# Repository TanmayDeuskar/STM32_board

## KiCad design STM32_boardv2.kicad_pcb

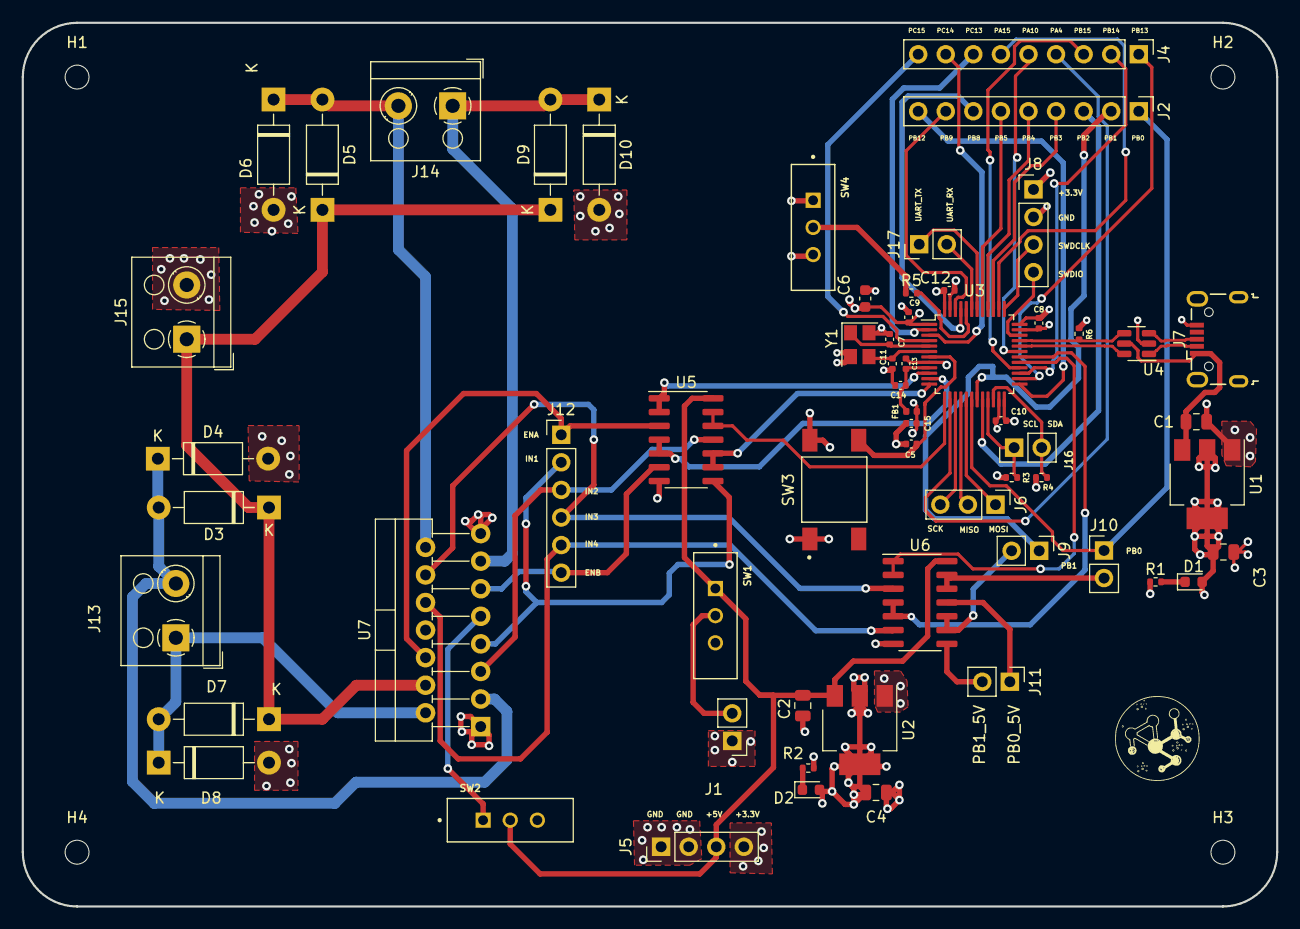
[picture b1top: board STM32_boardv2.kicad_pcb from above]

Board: 4 copper layers, 115.5 x 81.4 mm, 64 parts (0 on the bottom side), 66 nets.

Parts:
C1, C2, C3, C4: 22u; C_0805_2012Metric
C5, C8, C9, C10, C12: 100n; C_0402_1005Metric
C6: 10u; C_0603_1608Metric
C7, C11: 27p; C_0402_1005Metric
C13: 10n; C_0402_1005Metric
C14, C15: 1u; C_0402_1005Metric
D1, D2: LED; LED_0603_1608Metric
D3, D4, D5, D6, D7, D8, D9, D10: 1N4007; D_DO-41_SOD81_P10.16mm_Horizontal
FB1: 120R; L_0402_1005Metric
H1, H2, H3, H4: MountingHole; MountingHole_2.2mm_M2
J1, J9, J10, J11, J16, J17: Conn_01x02_Pin; PinHeader_1x02_P2.54mm_Vertical
J2, J4: Conn_01x09_Pin; PinHeader_1x09_P2.54mm_Vertical
J5, J8: Conn_01x04_Pin; PinHeader_1x04_P2.54mm_Vertical
J6: Conn_01x03_Pin; PinHeader_1x03_P2.54mm_Vertical
J7: USB_B_Micro; USB_Micro-B_Wuerth_629105150521
J12: Conn_01x06_Pin; PinHeader_1x06_P2.54mm_Vertical
J13, J14, J15: Screw_Terminal_01x02; TerminalBlock_RND_205-00001_1x02_P5.00mm_Horizontal
R1, R2, R3, R4, R6: 1K5; R_0402_1005Metric
R5: 10K; R_0402_1005Metric
SW1, SW2, SW4: SW_SPDT; SW_MINI-SPDT-SW
SW3: SW_MEC_5G; SW_4-1437565-1
U1, U2: AMS1117-3.3; SOT-223-3_TabPin2
U3: STM32F103C8T6; LQFP-48_7x7mm_P0.5mm
U4: USBLC6-2SC6; SOT-23-6
U5, U6: SN74HCT08N; SO-14_3.9x8.65mm_P1.27mm
U7: L298N; TO-220-15_P2.54x2.54mm_StaggerOdd_Lead4.58mm_Vertical
Y1: 16MHz; Crystal_SMD_3225-4Pin_3.2x2.5mm

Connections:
+3.3V: C3.1, C4.1, C6.1, C8.1, C9.1, C10.1, C12.1, C15.1, D1.2 (A), D2.2 (A), FB1.2, J5.4, J8.1, R3.1, R4.1, R6.1, SW4.3 (C), U1.2 (VO), U2.2 (VO), U3.1 (VBAT), U3.24 (VDD), U3.36 (VDD), U3.48 (VDD)
+3.3VA: C13.1, C14.1, FB1.1, U3.9 (VDDA)
+5V: C2.1, J5.3, SW1.1 (A), SW2.2 (B), U2.3 (VI), U5.14 (VCC), U6.14 (VCC)
+12V: D3.1 (K), D5.1 (K), D7.1 (K), D9.1 (K), J15.1, U7.4 (Vs)
/BOOT0: R5.2, U3.44 (BOOT0)
/CR_IN: C7.1, U3.5 (PD0), Y1.1
/CR_OUT: C11.1, U3.6 (PD1), Y1.3
/I2C2_SCL: J16.1, R3.2, U3.21 (PB10)
/I2C2_SDA: J16.2, R4.2, U3.22 (PB11)
/NRST: C5.1, SW3.3 (B), SW3.4 (B), U3.7 (NRST)
/SPI1_MISO: J6.2, U3.16 (PA6)
/SPI1_MOSI: J6.1, U3.17 (PA7)
/SPI1_SCK: J6.3, U3.15 (PA5)
/SWDCLK: J8.3, U3.37 (PA14)
/SWDIO: J8.4, U3.34 (PA13)
/SW_BOOT0: R5.1, SW4.2 (B)
/USART1_RX: J17.2, U3.43 (PB7)
/USART1_TX: J17.1, U3.42 (PB6)
/USB_CONN_D+: J7.3 (D+), U4.3 (I/O2)
/USB_CONN_D-: J7.2 (D-), U4.1 (I/O1)
/VIN: J1.2, SW1.2 (B)
ENA: J12.1, U5.3 (1Y), U7.6 (EnA)
ENB: J12.6, U5.6 (2Y), U7.11 (EnB)
GND: C1.2, C2.2, C3.2, C4.2, C5.2, C6.2, C7.2, C8.2, C9.2, C10.2, C11.2, C12.2, C13.2, C14.2, C15.2, D4.2 (A), D6.2 (A), D8.2 (A), D10.2 (A), J1.1, J5.1, J5.2, J7.5 (GND), J8.2, J15.2, R1.1, R2.1, SW3.1 (A), SW3.2 (A), SW4.1 (A), U1.1 (GND), U2.1 (GND), U3.8 (VSSA), U3.23 (VSS), U3.35 (VSS), U3.47 (VSS), U4.2 (GND), U5.7 (GND), U6.7 (GND), U7.1 (SENSE_A), U7.8 (GND), U7.15 (SENSE_B), Y1.2, Y1.4
IN1: J12.2, U5.8 (3Y), U7.7 (IN2)
IN2: J12.3, U5.11 (4Y), U7.5 (IN1)
IN3: J12.4, U6.3 (1Y), U7.12 (IN4)
IN4: J12.5, U6.6 (2Y), U7.10 (IN3)
unnamed: D1.1 (K), R1.2
unnamed: D2.1 (K), R2.2
unnamed: J9.2, U6.9 (3A), U6.10 (3B)
unnamed: J10.2, U6.12 (4A), U6.13 (4B)
unnamed: J11.1, U6.11 (4Y)
unnamed: J11.2, U6.8 (3Y)
unnamed: SW2.1 (A), U7.9 (Vss)
unnamed: U3.10 (PA0), U5.1 (1A), U5.2 (1B)
unnamed: U3.11 (PA1), U5.4 (2A), U5.5 (2B)
unnamed: U3.12 (PA2), U5.9 (3A), U5.10 (3B)
unnamed: U3.13 (PA3), U5.12 (4A), U5.13 (4B)
OUT1: D7.2 (A), D8.1 (K), J13.1, U7.2 (OUT1)
OUT2: D3.2 (A), D4.1 (K), J13.2, U7.3 (OUT2)
OUT3: D9.2 (A), D10.1 (K), J14.1, U7.13 (OUT3)
OUT4: D5.2 (A), D6.1 (K), J14.2, U7.14 (OUT4)
PA4: J4.4, U3.14 (PA4)
PA10: J4.5, U3.31 (PA10)
PA15: J4.6, U3.38 (PA15)
PB0: J2.1, J10.1, U3.18 (PB0)
PB1: J2.2, J9.1, U3.19 (PB1)
PB2: J2.3, U3.20 (PB2)
PB3: J2.4, U3.39 (PB3)
PB4: J2.5, U3.40 (PB4)
PB5: J2.6, U3.41 (PB5)
PB8: J2.7, U3.45 (PB8)
PB9: J2.8, U3.46 (PB9)
PB12: J2.9, U3.25 (PB12)
PB13: J4.1, U3.26 (PB13)
PB14: J4.2, U3.27 (PB14)
PB15: J4.3, U3.28 (PB15)
PC13: J4.7, U3.2 (PC13)
PC14: J4.8, U3.3 (PC14)
PC15: J4.9, U3.4 (PC15)
U4_1A: U3.29 (PA8), U6.1 (1A), U6.2 (1B)
U4_1B: U3.30 (PA9), U6.4 (2A), U6.5 (2B)
USB_D+: R6.2, U3.33 (PA12), U4.4 (I/O2)
USB_D-: U3.32 (PA11), U4.6 (I/O1)
VBUS: C1.1, J7.1 (VBUS), U1.3 (VI), U4.5 (VBUS)

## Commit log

2023-09-15 commit 16/9
2023-10-23 STM32V2
